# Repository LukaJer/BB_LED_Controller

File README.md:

# LED Controller

## will probably run WLED
- ArtNet via WLAN
- wired DMX

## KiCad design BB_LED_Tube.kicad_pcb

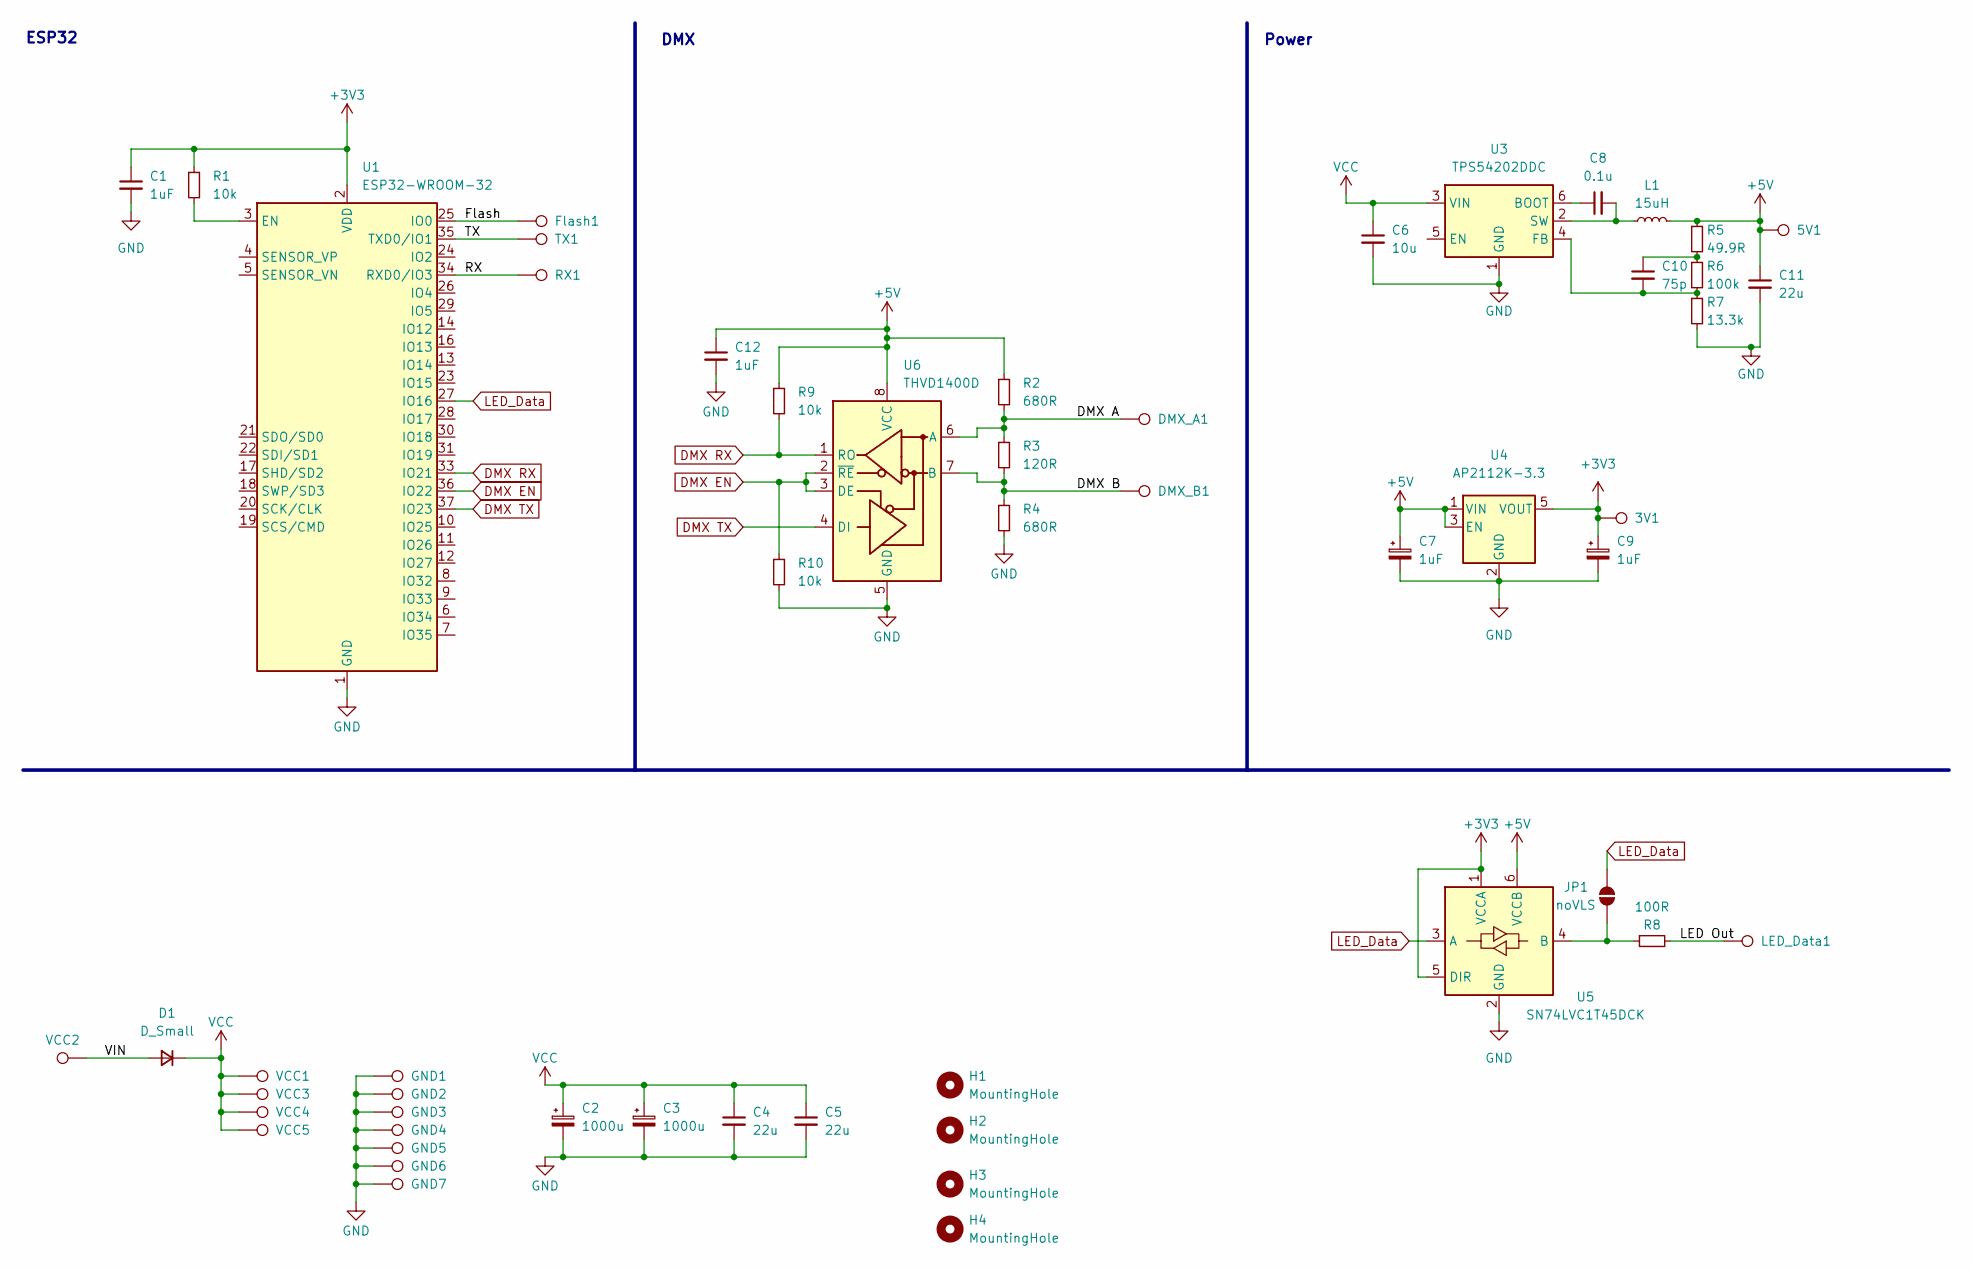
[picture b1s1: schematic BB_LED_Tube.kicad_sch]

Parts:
3V1, 5V1: TestPoint; TestPoint_Pad_D1.5mm
C1, C7, C9, C12: 1uF; C_0603_1608Metric
C2, C3: 1000u; CP_Elec_10x12.6
C4, C5, C11: 22u; C_0805_2012Metric
C6: 10u; C_0805_2012Metric
C8: 0.1u; C_0603_1608Metric
C10: 75p; C_0603_1608Metric
D1: D_Small; D_SMB
DMX_A1: TestPoint; TestPoint_THTPad_D2.0mm_Drill1.0mm
DMX_B1: TestPoint; TestPoint_THTPad_D2.0mm_Drill1.0mm
Flash1: TestPoint; TestPoint_Pad_D1.5mm
GND1, GND2, GND3, GND4, GND5: TestPoint; TestPoint_THTPad_D3.0mm_Drill1.5mm
GND6: TestPoint; TestPoint_THTPad_D2.0mm_Drill1.0mm
GND7: TestPoint; TestPoint_Pad_D1.5mm
H1, H2, H3, H4: MountingHole; MountingHole_2.7mm_M2.5
JP1: noVLS; SolderJumper-2_P1.3mm_Open_RoundedPad1.0x1.5mm
L1: 15uH; L_APV_ANR4020
LED_Data1: TestPoint; TestPoint_THTPad_D2.0mm_Drill1.0mm
R1, R9, R10: 10k; R_0603_1608Metric
R2, R4: 680R; R_0805_2012Metric
R3: 120R; R_0805_2012Metric
R5: 49.9R; R_0603_1608Metric
R6: 100k; R_0603_1608Metric
R7: 13.3k; R_0603_1608Metric
R8: 100R; R_0603_1608Metric
RX1: TestPoint; TestPoint_Pad_D1.5mm
TX1: TestPoint; TestPoint_Pad_D1.5mm
U1: ESP32-WROOM-32
U3: TPS54202DDC; SOT-23-6
U4: AP2112K-3.3; SOT-23-5
U5: SN74LVC1T45DCK; SOT-363_SC-70-6
U6: THVD1400D; SOT-583-8
VCC1, VCC2, VCC3, VCC4, VCC5: TestPoint; TestPoint_THTPad_D3.0mm_Drill1.5mm

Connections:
+3V3: 3V1.1, C1.1, C9.1, R1.1, U1.2 (VDD), U4.5 (VOUT), U5.1 (VCCA), U5.5 (DIR)
+5V: 5V1.1, C7.1, C11.1, C12.1, L1.2, R2.1, R5.1, R9.1, U4.1 (VIN), U4.3 (EN), U5.6 (VCCB), U6.8 (VCC)
/DMX A: DMX_A1.1, R2.2, R3.1, U6.6 (A)
/DMX B: DMX_B1.1, R3.2, R4.1, U6.7 (B)
/Flash: Flash1.1, U1.25 (IO0)
/LED Out: LED_Data1.1, R8.2
/RX: RX1.1, U1.34 (RXD0/IO3)
/TX: TX1.1, U1.35 (TXD0/IO1)
/VIN: D1.2 (A), VCC2.1
DMX EN: R10.1, U1.36 (IO22), U6.2 (~RE), U6.3 (DE)
DMX RX: R9.2, U1.33 (IO21), U6.1 (RO)
DMX TX: U1.37 (IO23), U6.4 (DI)
GND: C1.2, C2.2, C3.2, C4.2, C5.2, C6.2, C7.2, C9.2, C11.2, C12.2, GND1.1, GND2.1, GND3.1, GND4.1, GND5.1, GND6.1, GND7.1, R4.2, R7.2, R10.2, U1.1 (GND), U1.15 (GND), U1.38 (GND), U1.39 (GND), U3.1 (GND), U4.2 (GND), U5.2 (GND), U6.5 (GND)
LED_Data: JP1.2 (B), U1.27 (IO16), U5.3 (A)
unnamed: C10.1, R5.2, R6.1
unnamed: JP1.1 (A), R8.1, U5.4 (B)
unnamed: R1.2, U1.3 (EN)
unnamed: C8.1, U3.6 (BOOT)
unnamed: C10.2, R6.2, R7.1, U3.4 (FB)
unnamed: C8.2, L1.1, U3.2 (SW)
VCC: C2.1, C3.1, C4.1, C5.1, C6.1, D1.1 (K), U3.3 (VIN), VCC1.1, VCC3.1, VCC4.1, VCC5.1

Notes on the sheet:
Power
DMX
ESP32

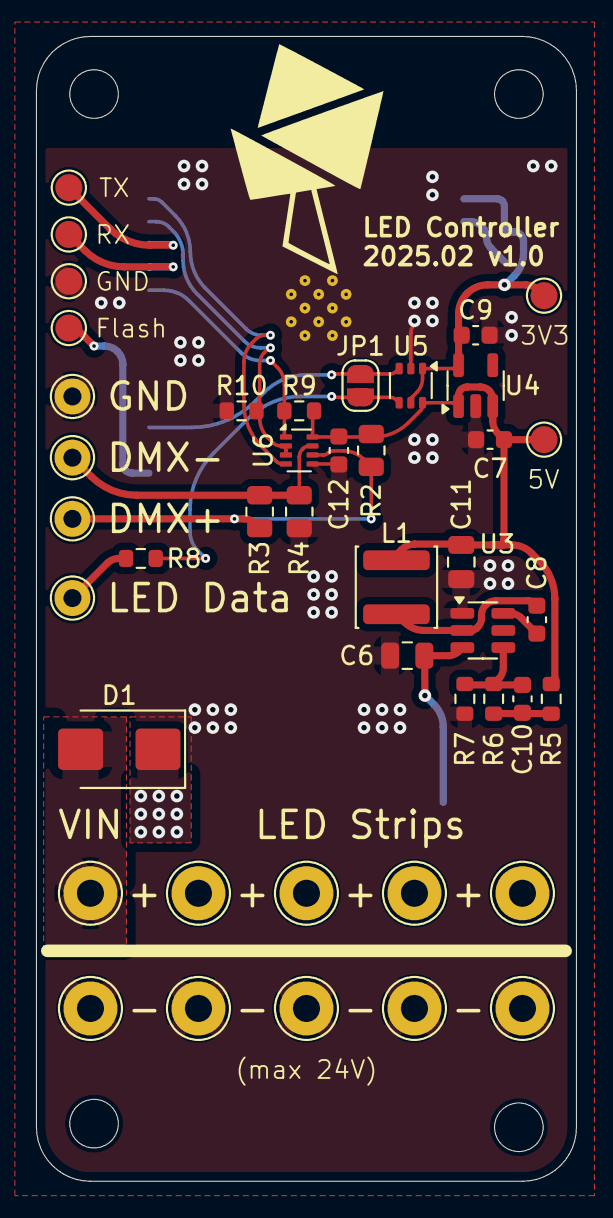
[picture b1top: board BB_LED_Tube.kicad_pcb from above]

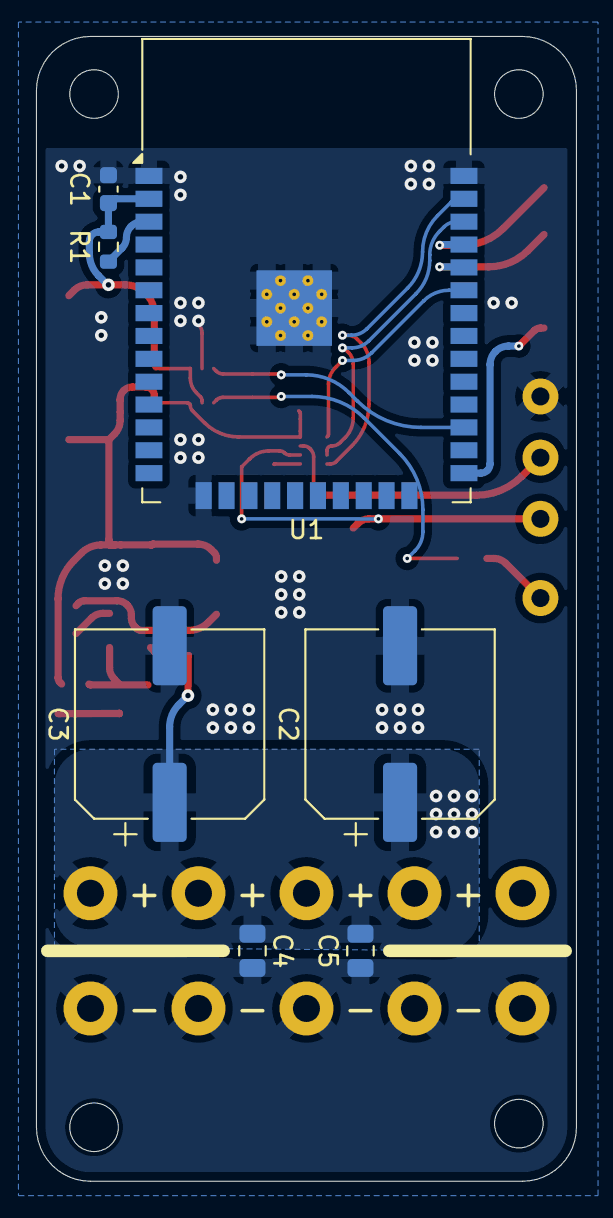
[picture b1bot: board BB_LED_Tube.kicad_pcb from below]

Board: 2 copper layers, 30.0 x 63.6 mm, 54 parts (7 on the bottom side), 21 nets.

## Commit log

2025-02-28 init
2025-02-28 added reverse voltage protection & more mounting holes
2025-02-28 small update
2025-03-01 added voltage shifter and exchanged RS485 chip
